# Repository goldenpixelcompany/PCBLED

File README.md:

# PCBLED v1
Hardware for controlling LED 24V

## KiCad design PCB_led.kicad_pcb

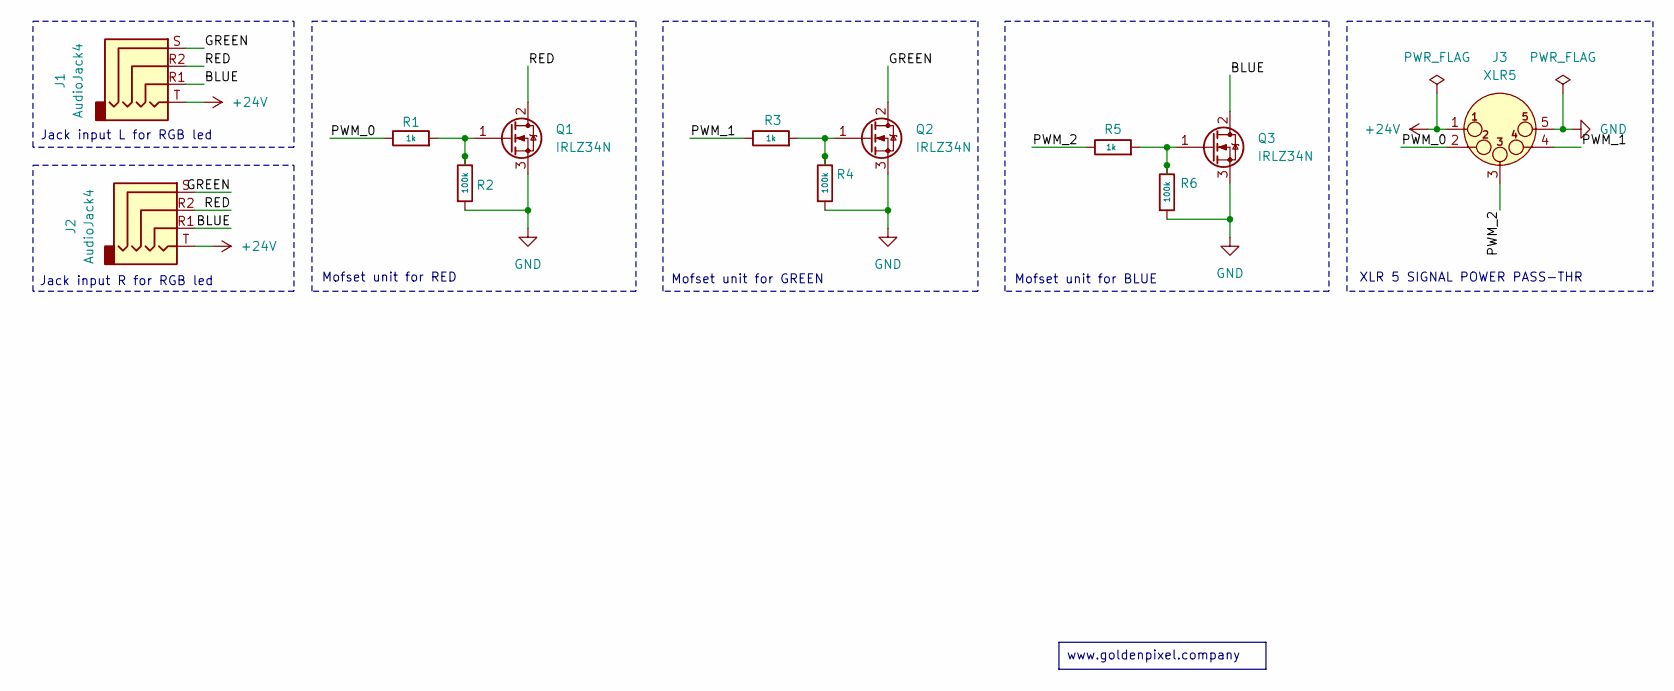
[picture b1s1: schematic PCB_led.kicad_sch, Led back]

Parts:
J1, J2: AudioJack4
J3: XLR5
Q1, Q2, Q3: IRLZ34N; TO-220-3_Vertical
R1, R3, R5: 1k
R2, R4, R6: 100k

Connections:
+24V: J1.T, J2.T, J3.1
/BLUE: J1.R1, J2.R1, Q3.2 (D)
/GREEN: J1.S, J2.S, Q2.2 (D)
/PWM_0: J3.2, R1.1
/PWM_1: J3.4 (P3), R3.1
/PWM_2: J3.3, R5.1
/RED: J1.R2, J2.R2, Q1.2 (D)
GND: J3.5, Q1.3 (S), Q2.3 (S), Q3.3 (S), R2.2, R4.2, R6.2
unnamed: Q1.1 (G), R1.2, R2.1
unnamed: Q2.1 (G), R3.2, R4.1
unnamed: Q3.1 (G), R5.2, R6.1

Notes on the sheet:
www.goldenpixel.company
Mofset unit for RED
Jack input L for RGB led
Mofset unit for BLUE
XLR 5 SIGNAL POWER PASS-THR
Mofset unit for GREEN
Jack input R for RGB led

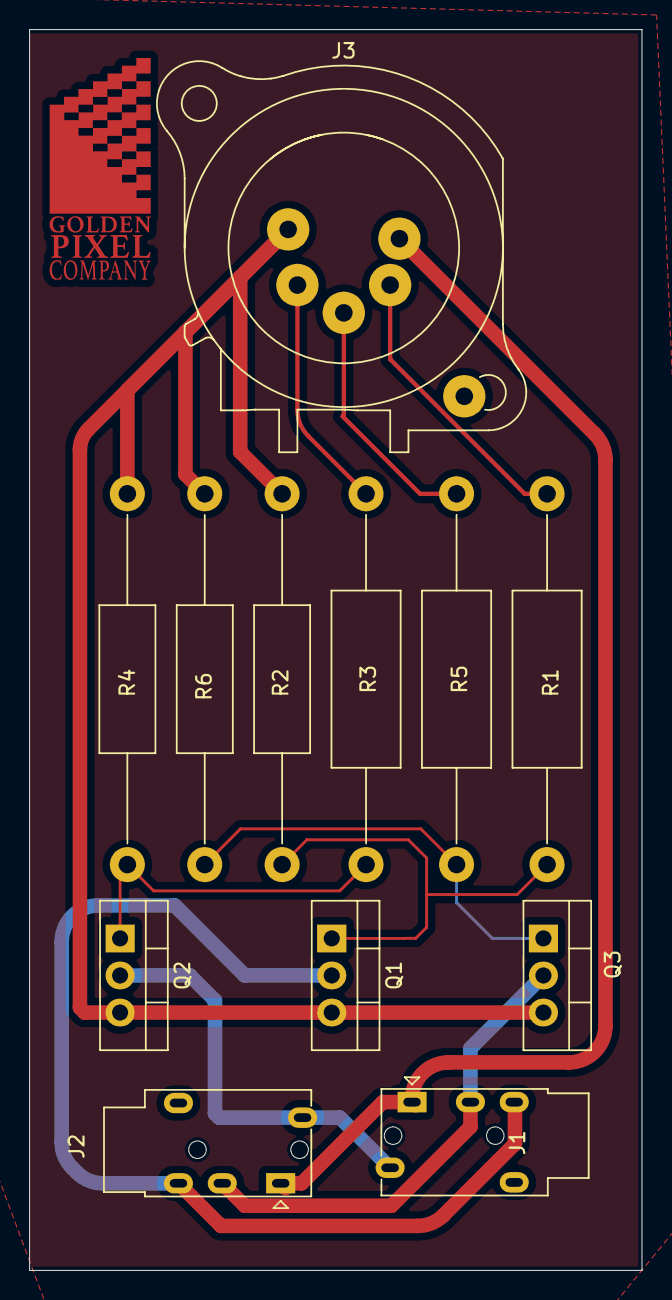
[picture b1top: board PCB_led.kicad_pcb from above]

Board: 2 copper layers, 42.0 x 85.0 mm, 12 parts (0 on the bottom side), 11 nets.
